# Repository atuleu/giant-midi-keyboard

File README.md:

# Giant MIDI Keyboard

This project is an open source Giant MIDI Keyboard, using an Arduino Micro, LUFA, and some small devices.

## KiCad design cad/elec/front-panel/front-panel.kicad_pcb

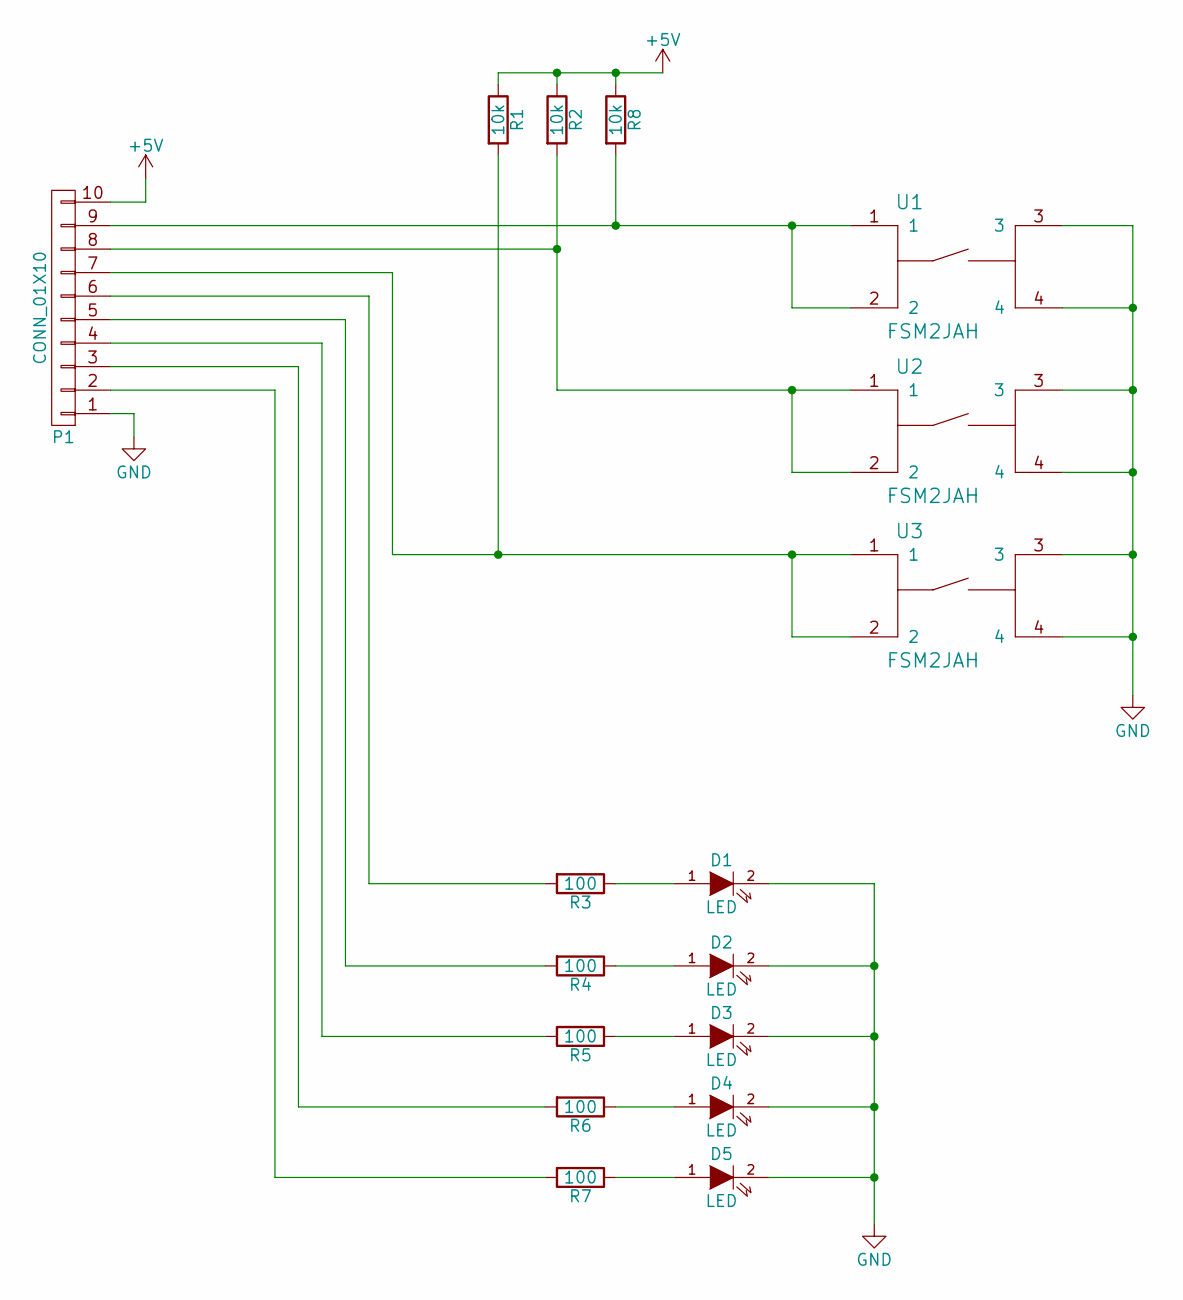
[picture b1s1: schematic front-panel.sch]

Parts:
D1, D2, D3, D4, D5: LED; LED-5MM; Part Number LC503FBL1-15Q-A3-00001
P1: CONN_01X10; Socket_Strip_Straight_2x05
R1, R2, R8: 10k; Resistor_Horizontal_RM10mm
R3, R4, R5, R6, R7: 100; Resistor_Horizontal_RM10mm
U1, U2, U3: FSM2JAH; Part Number FSM2JAH

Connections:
+5V: P1.10, R1.1, R2.1, R8.1
GND: D1.2 (K), D2.2 (K), D3.2 (K), D4.2 (K), D5.2 (K), P1.1, U1.3, U1.4, U2.3, U2.4, U3.3, U3.4
unnamed: D1.1 (A), R3.1
unnamed: D2.1 (A), R4.1
unnamed: D3.1 (A), R5.1
unnamed: D4.1 (A), R6.1
unnamed: D5.1 (A), R7.1
unnamed: P1.2, R7.2
unnamed: P1.3, R6.2
unnamed: P1.4, R5.2
unnamed: P1.5, R4.2
unnamed: P1.6, R3.2
unnamed: P1.7, R1.2, U3.1, U3.2
unnamed: P1.8, R2.2, U2.1, U2.2
unnamed: P1.9, R8.2, U1.1, U1.2

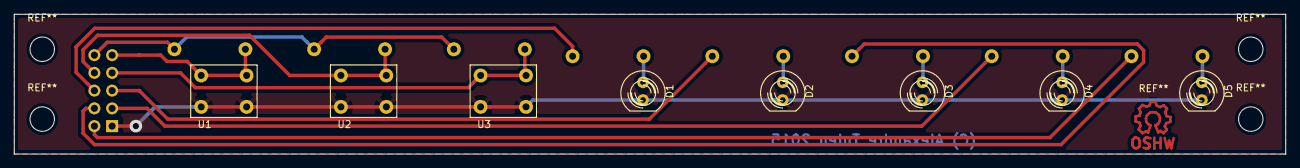
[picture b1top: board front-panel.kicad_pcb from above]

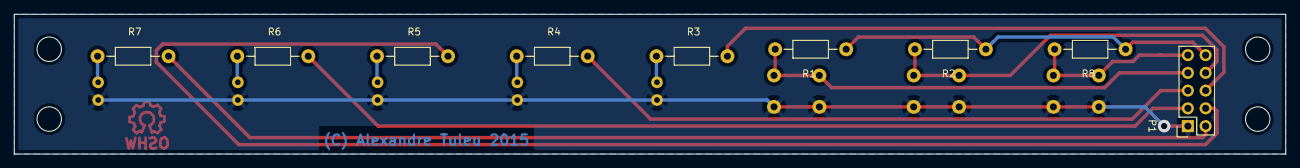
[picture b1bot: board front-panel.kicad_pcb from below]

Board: 2 copper layers, 182.0 x 20.0 mm, 17 parts (9 on the bottom side), 15 nets.

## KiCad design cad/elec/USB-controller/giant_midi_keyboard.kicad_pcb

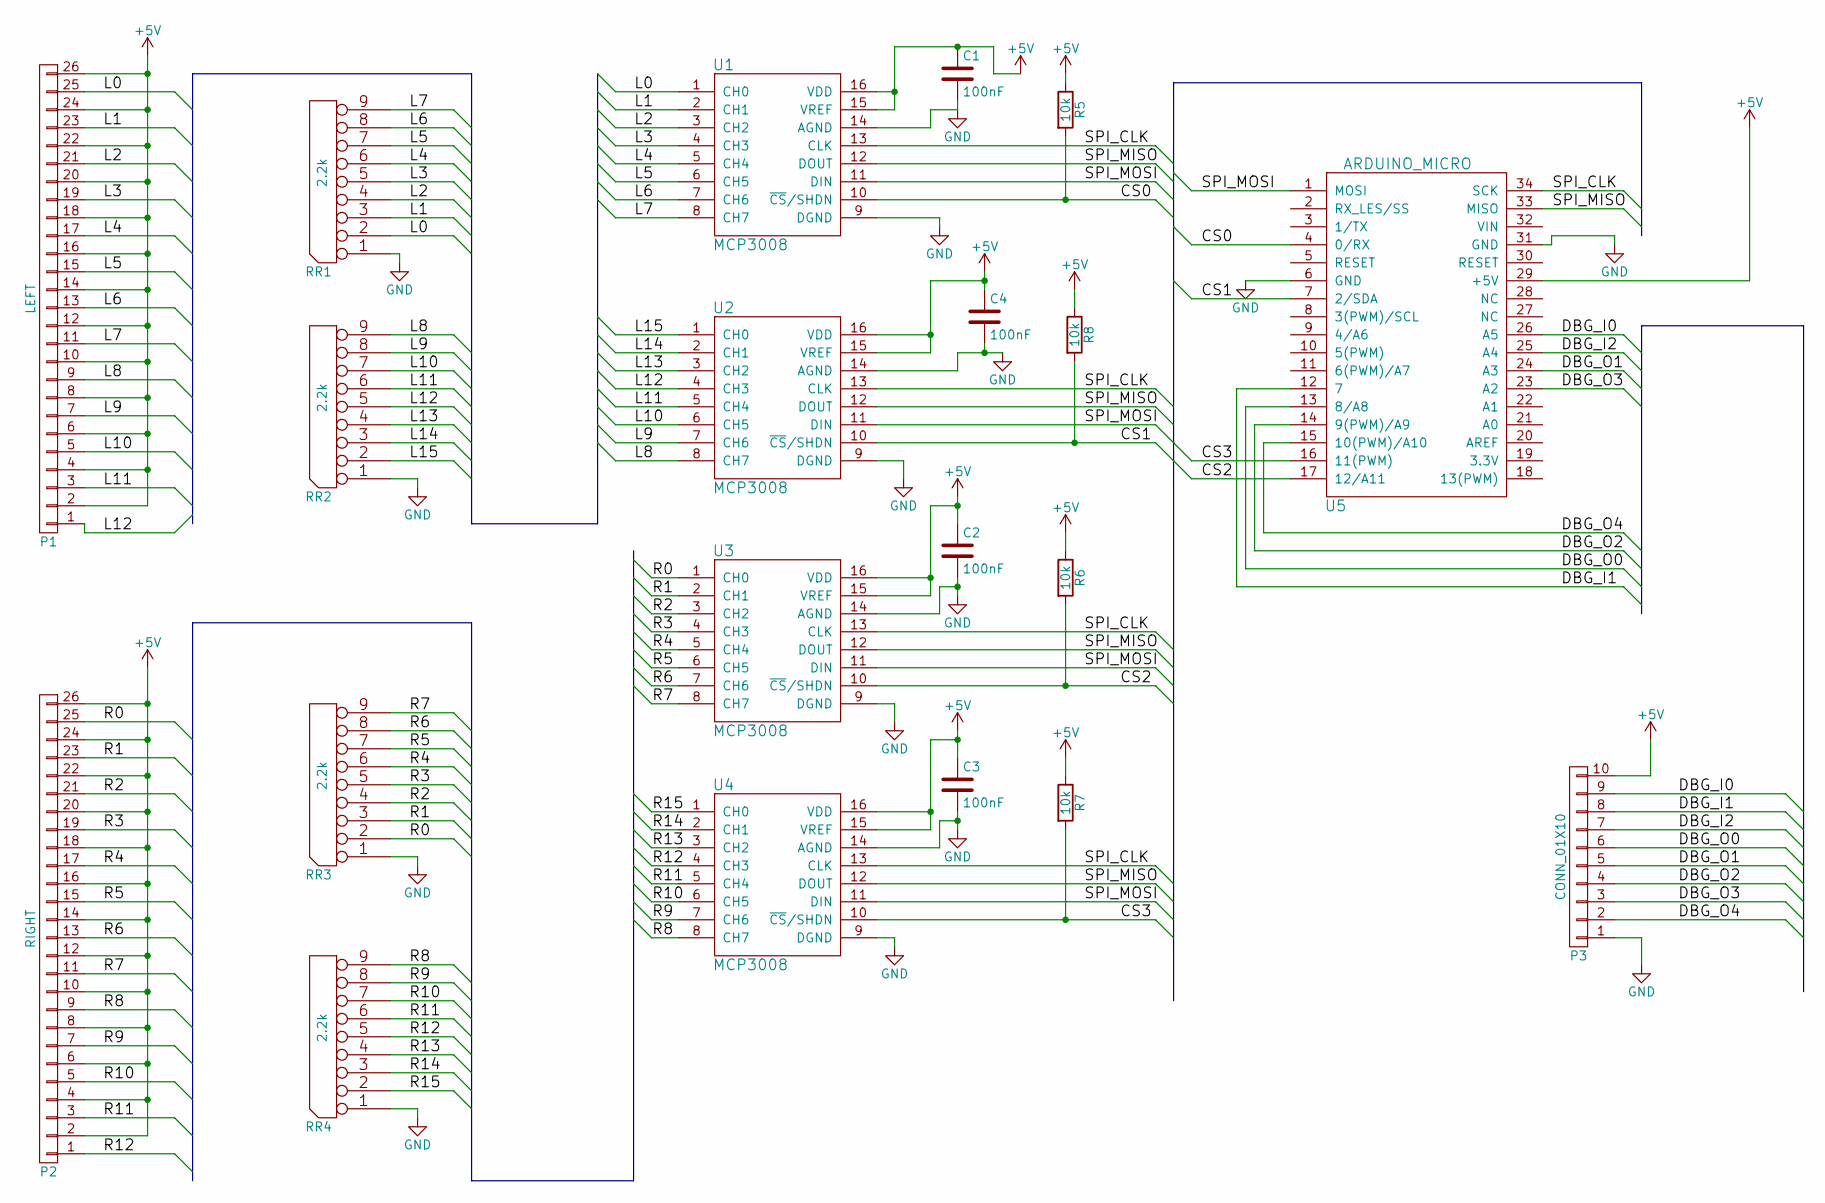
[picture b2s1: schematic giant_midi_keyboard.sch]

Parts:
C1, C2, C3, C4: 100nF; C_Disc_D6_P5; Part Number MC0805B104K500A2.54MM
P1: LEFT; Header_2x13; Part Number T821126A1S100CEU
P2: RIGHT; Header_2x13; Part Number T821126A1S100CEU
P3: CONN_01X10; Header_2x5
R5, R6, R7, R8: 10k; Resistor_Horizontal_RM10mm
RR1, RR2, RR3, RR4: 2.2k; SIP9_Housing_BigPads; Part Number 4609X-101-222LF
U1, U2, U3, U4: MCP3008; DIP-16__300_ELL; Part Number MCP3008-I/P
U5: ARDUINO_MICRO; Part Number Arduino Micro

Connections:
+5V: C1.1, C2.1, C3.1, C4.1, P1.2, P1.4, P1.6, P1.8, P1.10, P1.12, P1.14, P1.16, P1.18, P1.20, P1.22, P1.24, P1.26, P2.2, P2.4, P2.6, P2.8, P2.10, P2.12, P2.14, P2.16, P2.18, P2.20, P2.22, P2.24, P2.26, P3.10, R5.1, R6.1, R7.1, R8.1, U1.15 (VREF), U1.16 (VDD), U2.15 (VREF), U2.16 (VDD), U3.15 (VREF), U3.16 (VDD), U4.15 (VREF), U4.16 (VDD), U5.29 (+5V)
/CS0: R5.2, U1.10 (~CS~/SHDN), U5.4 (0/RX)
/CS1: R8.2, U2.10 (~CS~/SHDN), U5.7 (2/SDA)
/CS2: R6.2, U3.10 (~CS~/SHDN), U5.17 (12/A11)
/CS3: R7.2, U4.10 (~CS~/SHDN), U5.16 (11(PWM))
/DBG_I0: P3.9, U5.26 (A5)
/DBG_I1: P3.8, U5.12 (7)
/DBG_I2: P3.7, U5.25 (A4)
/DBG_O0: P3.6, U5.13 (8/A8)
/DBG_O1: P3.5, U5.24 (A3)
/DBG_O2: P3.4, U5.14 (9(PWM)/A9)
/DBG_O3: P3.3, U5.23 (A2)
/DBG_O4: P3.2, U5.15 (10(PWM)/A10)
/L0: P1.25, RR1.2, U1.1 (CH0)
/L1: P1.23, RR1.3, U1.2 (CH1)
/L2: P1.21, RR1.4, U1.3 (CH2)
/L3: P1.19, RR1.5, U1.4 (CH3)
/L4: P1.17, RR1.6, U1.5 (CH4)
/L5: P1.15, RR1.7, U1.6 (CH5)
/L6: P1.13, RR1.8, U1.7 (CH6)
/L7: P1.11, RR1.9, U1.8 (CH7)
/L8: P1.9, RR2.9, U2.8 (CH7)
/L9: P1.7, RR2.8, U2.7 (CH6)
/L10: P1.5, RR2.7, U2.6 (CH5)
/L11: P1.3, RR2.6, U2.5 (CH4)
/L12: P1.1, RR2.5, U2.4 (CH3)
/L13: RR2.4, U2.3 (CH2)
/L14: RR2.3, U2.2 (CH1)
/L15: RR2.2, U2.1 (CH0)
/R0: P2.25, RR3.2, U3.1 (CH0)
/R1: P2.23, RR3.3, U3.2 (CH1)
/R2: P2.21, RR3.4, U3.3 (CH2)
/R3: P2.19, RR3.5, U3.4 (CH3)
/R4: P2.17, RR3.6, U3.5 (CH4)
/R5: P2.15, RR3.7, U3.6 (CH5)
/R6: P2.13, RR3.8, U3.7 (CH6)
/R7: P2.11, RR3.9, U3.8 (CH7)
/R8: P2.9, RR4.9, U4.8 (CH7)
/R9: P2.7, RR4.8, U4.7 (CH6)
/R10: P2.5, RR4.7, U4.6 (CH5)
/R11: P2.3, RR4.6, U4.5 (CH4)
/R12: P2.1, RR4.5, U4.4 (CH3)
/R13: RR4.4, U4.3 (CH2)
/R14: RR4.3, U4.2 (CH1)
/R15: RR4.2, U4.1 (CH0)
/SPI_CLK: U1.13 (CLK), U2.13 (CLK), U3.13 (CLK), U4.13 (CLK), U5.34 (SCK)
/SPI_MISO: U1.12 (DOUT), U2.12 (DOUT), U3.12 (DOUT), U4.12 (DOUT), U5.33 (MISO)
/SPI_MOSI: U1.11 (DIN), U2.11 (DIN), U3.11 (DIN), U4.11 (DIN), U5.1 (MOSI)
GND: C1.2, C2.2, C3.2, C4.2, P3.1, RR1.1 (COM), RR2.1 (COM), RR3.1 (COM), RR4.1 (COM), U1.9 (DGND), U1.14 (AGND), U2.9 (DGND), U2.14 (AGND), U3.9 (DGND), U3.14 (AGND), U4.9 (DGND), U4.14 (AGND), U5.6 (GND), U5.31 (GND)

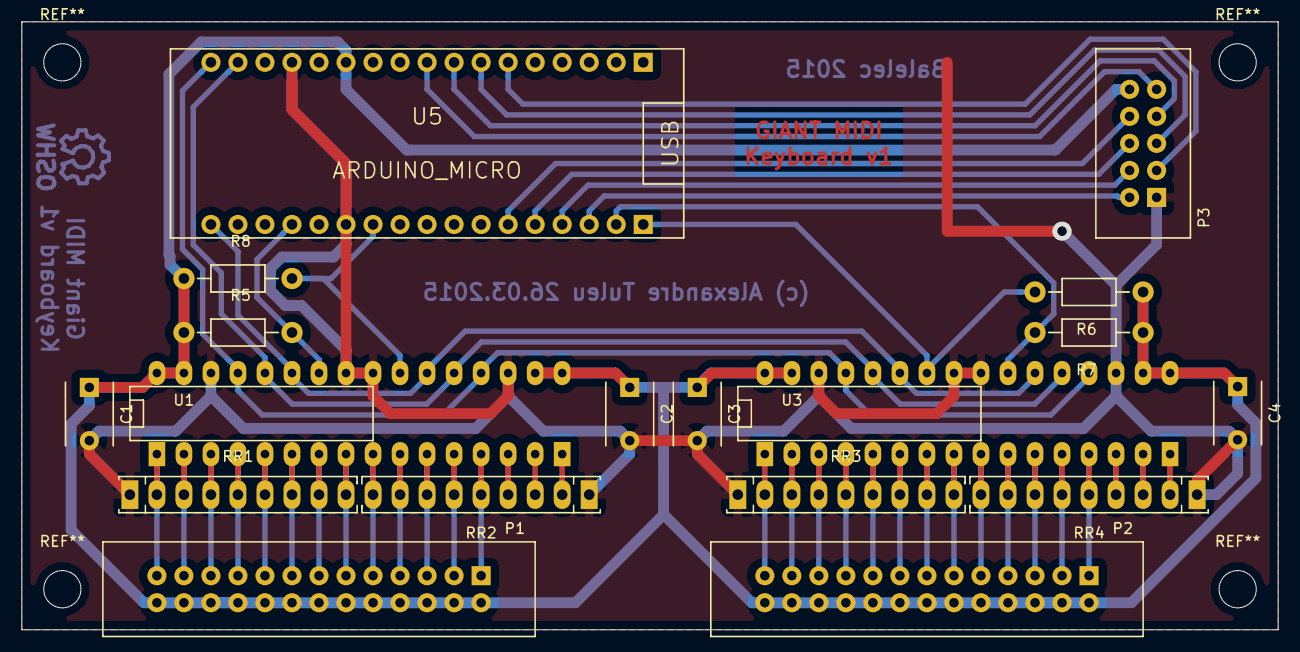
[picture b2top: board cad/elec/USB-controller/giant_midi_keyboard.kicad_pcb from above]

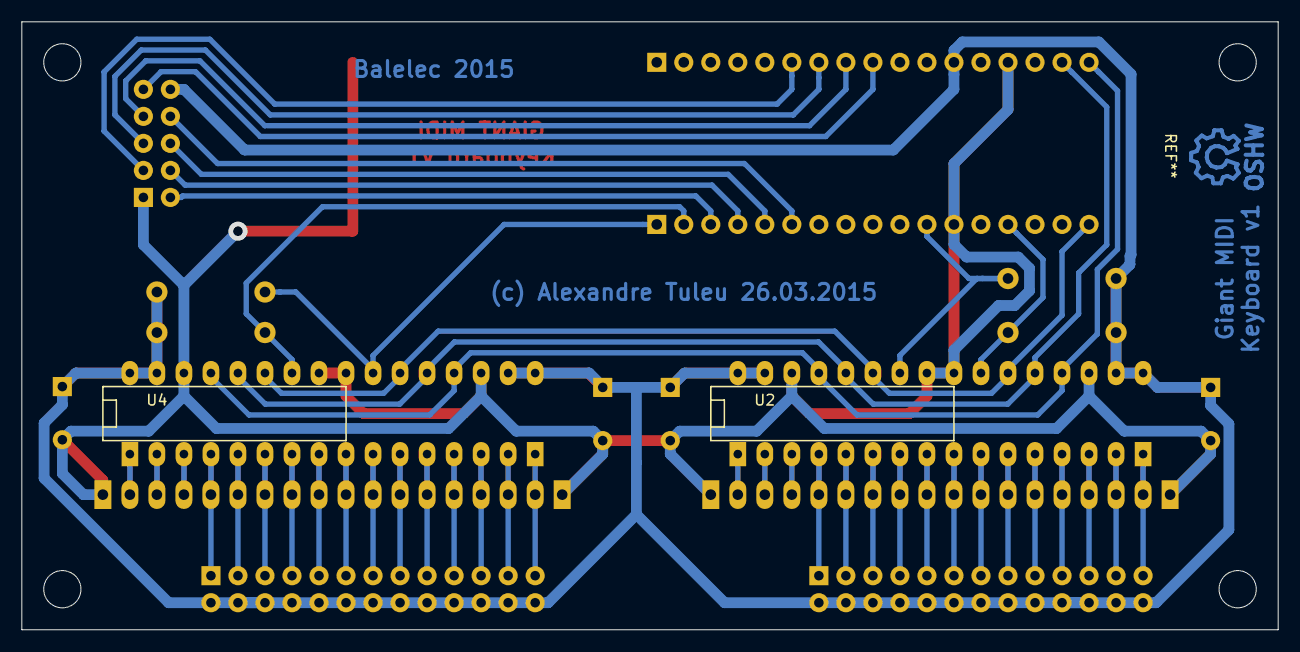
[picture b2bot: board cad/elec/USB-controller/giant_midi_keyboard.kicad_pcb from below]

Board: 2 copper layers, 118.1 x 57.1 mm, 20 parts (2 on the bottom side), 49 nets.

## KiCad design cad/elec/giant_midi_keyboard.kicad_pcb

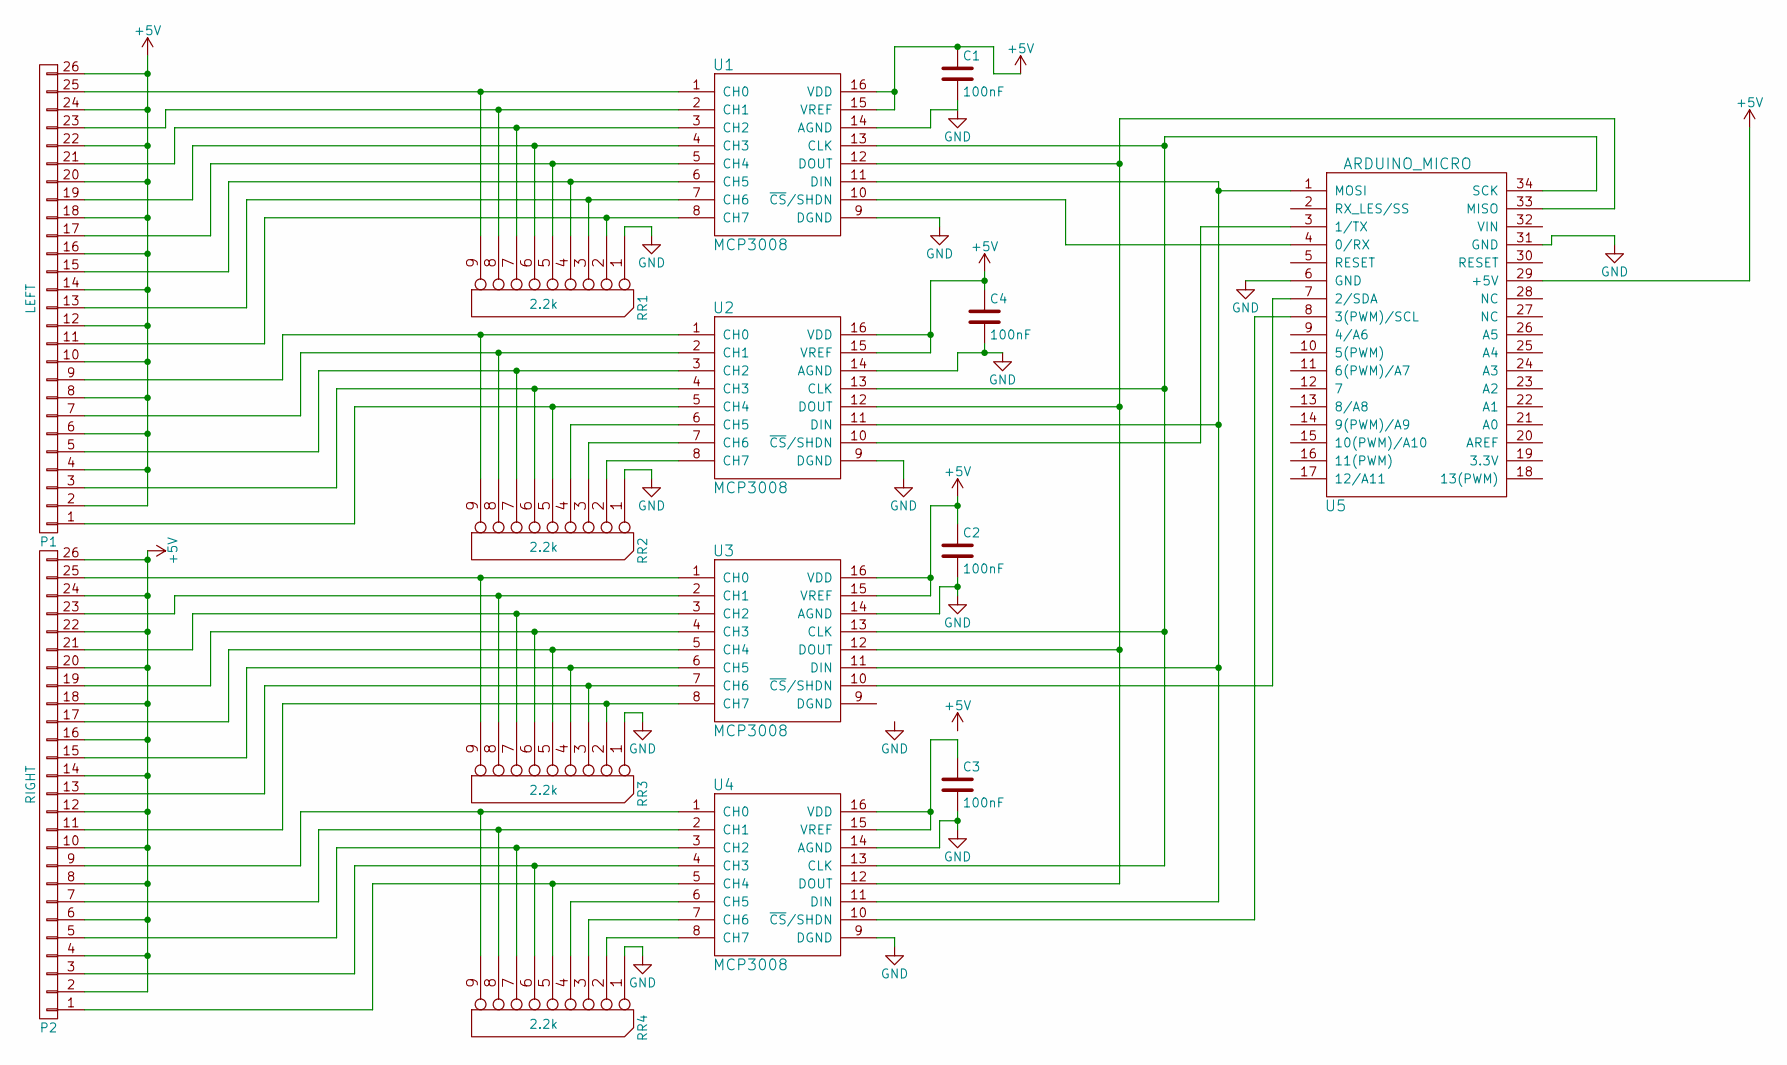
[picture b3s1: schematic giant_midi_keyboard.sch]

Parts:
C1, C2, C3, C4: 100nF; C_Disc_D6_P5; Part Number MC0805B104K500A2.54MM
P1: LEFT; Pin_Header_Straight_2x13; Part Number T816126A1S101CEU
P2: RIGHT; Pin_Header_Straight_2x13; Part Number T816126A1S101CEU
RR1, RR2, RR3, RR4: 2.2k; SIP9_Housing_BigPads; Part Number 4609X-101-222LF
U1, U2, U3, U4: MCP3008; DIP-16__300_ELL; Part Number MCP3008-I/P
U5: ARDUINO_MICRO; Part Number Arduino Micro

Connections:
+5V: C1.1, C2.1, C4.1, P1.2, P1.4, P1.6, P1.8, P1.10, P1.12, P1.14, P1.16, P1.18, P1.20, P1.22, P1.24, P1.26, P2.2, P2.4, P2.6, P2.8, P2.10, P2.12, P2.14, P2.16, P2.18, P2.20, P2.22, P2.24, P2.26, U1.15 (VREF), U1.16 (VDD), U2.15 (VREF), U2.16 (VDD), U3.15 (VREF), U3.16 (VDD), U5.29 (+5V)
GND: C1.2, C2.2, C3.2, C4.2, RR1.1 (COM), RR2.1 (COM), RR3.1 (COM), RR4.1 (COM), U1.9 (DGND), U1.14 (AGND), U2.9 (DGND), U2.14 (AGND), U3.14 (AGND), U4.9 (DGND), U4.14 (AGND), U5.6 (GND), U5.31 (GND)
unnamed: C3.1, U4.15 (VREF), U4.16 (VDD)
unnamed: P1.1, RR2.5, U2.5 (CH4)
unnamed: P1.3, RR2.6, U2.4 (CH3)
unnamed: P1.5, RR2.7, U2.3 (CH2)
unnamed: P1.7, RR2.8, U2.2 (CH1)
unnamed: P1.9, RR2.9, U2.1 (CH0)
unnamed: P1.11, RR1.2, U1.8 (CH7)
unnamed: P1.13, RR1.3, U1.7 (CH6)
unnamed: P1.15, RR1.4, U1.6 (CH5)
unnamed: P1.17, RR1.5, U1.5 (CH4)
unnamed: P1.19, RR1.6, U1.4 (CH3)
unnamed: P1.21, RR1.7, U1.3 (CH2)
unnamed: P1.23, RR1.8, U1.2 (CH1)
unnamed: P1.25, RR1.9, U1.1 (CH0)
unnamed: P2.1, RR4.5, U4.5 (CH4)
unnamed: P2.3, RR4.6, U4.4 (CH3)
unnamed: P2.5, RR4.7, U4.3 (CH2)
unnamed: P2.7, RR4.8, U4.2 (CH1)
unnamed: P2.9, RR4.9, U4.1 (CH0)
unnamed: P2.11, RR3.2, U3.8 (CH7)
unnamed: P2.13, RR3.3, U3.7 (CH6)
unnamed: P2.15, RR3.4, U3.6 (CH5)
unnamed: P2.17, RR3.5, U3.5 (CH4)
unnamed: P2.19, RR3.6, U3.4 (CH3)
unnamed: P2.21, RR3.7, U3.3 (CH2)
unnamed: P2.23, RR3.8, U3.2 (CH1)
unnamed: P2.25, RR3.9, U3.1 (CH0)
unnamed: RR2.2, U2.8 (CH7)
unnamed: RR2.3, U2.7 (CH6)
unnamed: RR2.4, U2.6 (CH5)
unnamed: RR4.2, U4.8 (CH7)
unnamed: RR4.3, U4.7 (CH6)
unnamed: RR4.4, U4.6 (CH5)
unnamed: U1.10 (~CS~/SHDN), U5.4 (0/RX)
unnamed: U1.11 (DIN), U2.11 (DIN), U3.11 (DIN), U4.11 (DIN), U5.1 (MOSI)
unnamed: U1.12 (DOUT), U2.12 (DOUT), U3.12 (DOUT), U4.12 (DOUT), U5.33 (MISO)
unnamed: U1.13 (CLK), U2.13 (CLK), U3.13 (CLK), U4.13 (CLK), U5.34 (SCK)
unnamed: U2.10 (~CS~/SHDN), U5.3 (1/TX)
unnamed: U3.10 (~CS~/SHDN), U5.7 (2/SDA)
unnamed: U4.10 (~CS~/SHDN), U5.8 (3(PWM)/SCL)

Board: 2 copper layers, 15 parts (0 on the bottom side), 42 nets, no tracks yet.

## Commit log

2015-03-26 Initial stuff
2015-03-26 Adds proper LICENSE file
2015-03-26 Adds AUTHORS file
2015-03-26 Adds COPYING information
2015-03-26 Adds CERN OHL v1.2 license for hardware
2015-03-26 Adds blank project for electronics
2015-03-26 Adds first schematics
2015-03-27 Draws first draft of schematics and layout.
2015-03-28 Adds all base pieces
2015-03-28 Places all components
2015-03-28 Adds hole for cables
2015-04-02 Adds push butoon to lib
2015-04-02 Adds front panel board
2015-04-02 Updates usb board for use with panel board
2015-04-02 Adds panelized version
2015-04-02 Moves project to subdirectory
2015-04-02 Makes the board ready for manual engraving
2015-04-07 Corrects a bad sketches
2015-04-07 Adds Box and Base_Under
2015-04-07 Adds Drawing
2015-04-15 Adds LUFA and arduino-cmake submodules
2015-04-15 Updates the .gitignore rules for panelized versions
2015-04-15 Adds skeletons for Arduino FW
2015-04-15 Adds basic configuration
    Most of the thing comes from trial and error testing from
    atuleu/giant-snes-gamepad
2015-04-15 Debugs : make a binary clock
2015-04-15 Tests error reporting
2015-04-15 Improves error reporting
2015-04-15 Adds UserInterface button reading
    It is a bit more complex as it seems, because we have to make sure that
    there is no bounce of the push button. The button has to be pushed for
    more than 50 ms in order to trigger a Push events.
    There is no support for release events.
2015-04-17 Refactors UserInterface
2015-04-17 Removes arduino-cmake submodule
2015-04-17 Adds toolchain from github.com/mkleeman/cmake-avr
2015-04-17 Adds avr toolchain
2015-04-17 Adds LUFAConfig from github.com/atuleu/giant-snes-gamepad
2015-04-17 Adds Descriptor from LUFA examples
    It adds descriptor from LUFA MIDI application examples. It removed the
    External MIDI Out descriptor, as we only want MIDI IN.
2015-04-17 Switches to a Low-Level driver
2015-04-17 Corrects minor toolchain errors
2015-04-17 Adds USB stack
2015-04-20 Turns it into D. Guetta Piano
2015-04-20 Uses arduino ISP instead of dragon
2015-04-20 Fixes a small bug where display was not correctly set
2015-04-20 Adds minimal interface for reading SPI
2015-04-20 Adds KeyReader note mapping
2015-04-22 Fixes bug that crashed device
2015-04-23 Adds communication common base
2015-04-24 Adds enum for errors
2015-04-24 Implements Registers module
2015-04-24 Implements Vendor Communication interface
2015-04-24 Adds ring buffering of events
2015-04-24 Adds skeleton for a calibrator tool
2015-04-24 Moves calibrator to tools/calibrator
2015-04-24 Adds main skeleton
2015-04-24 Skeleton fo Qt application
2015-04-24 Adds a blank main window
2015-04-24 Basic layouting
2015-04-27 Remade the interface
2015-04-27 Adds glog logging
2015-04-27 Adds Interface for USB device
2015-04-27 Makes application cleaner to error
2015-04-27 Implements device look up
2015-04-27 Adds fetching of product and manufacturer key
2015-04-27 Parses product strings by interface
2015-04-27 Fixes swap between product and manufacturer strings
2015-04-27 Implements auto selection of devices
2015-04-27 Implements action Save in EEPROM
2015-04-27 fixes bug with refreshes
2015-04-27 Display cells in table
2015-04-28 Switches to Qt5
2015-04-28 Adds a plot surface for data
2015-04-28 Adds an Oscilloscope Widget template
2015-04-28 Adds Oscilloscope slots interface
2015-04-28 Updates UI for Oscilloscope
2015-04-28 Adds dynamic scales
2015-04-28 Implements plots function
2015-04-28 Debugs plotting of value with fake data
2015-04-28 Implements trigger functions
2015-04-29 Fixes small UI glitches
2015-04-29 Adds cmake support for translation
2015-04-29 corrects ts file generation
2015-04-29 Adds french translation
2015-04-29 Makes labels translatable
2015-04-29 Finishes french translation draft
2015-04-29 Install translation from system locale
2015-04-29 Implements cell report
2015-04-29 Implements fetching of values
2015-04-29 fixes communications
2015-04-29 Fixes device reading
2015-04-29 Prints with symbols
2015-04-29 Implements reading of registers
2015-04-29 Implements setting of registers
2015-04-29 Implements Save in EEPROM
2015-05-06 fixes stupid anoying bug
2015-05-06 Swaps the key pins
    It was an error on the schematics
2015-05-06 Working processing of keys
2015-05-06 A working process
